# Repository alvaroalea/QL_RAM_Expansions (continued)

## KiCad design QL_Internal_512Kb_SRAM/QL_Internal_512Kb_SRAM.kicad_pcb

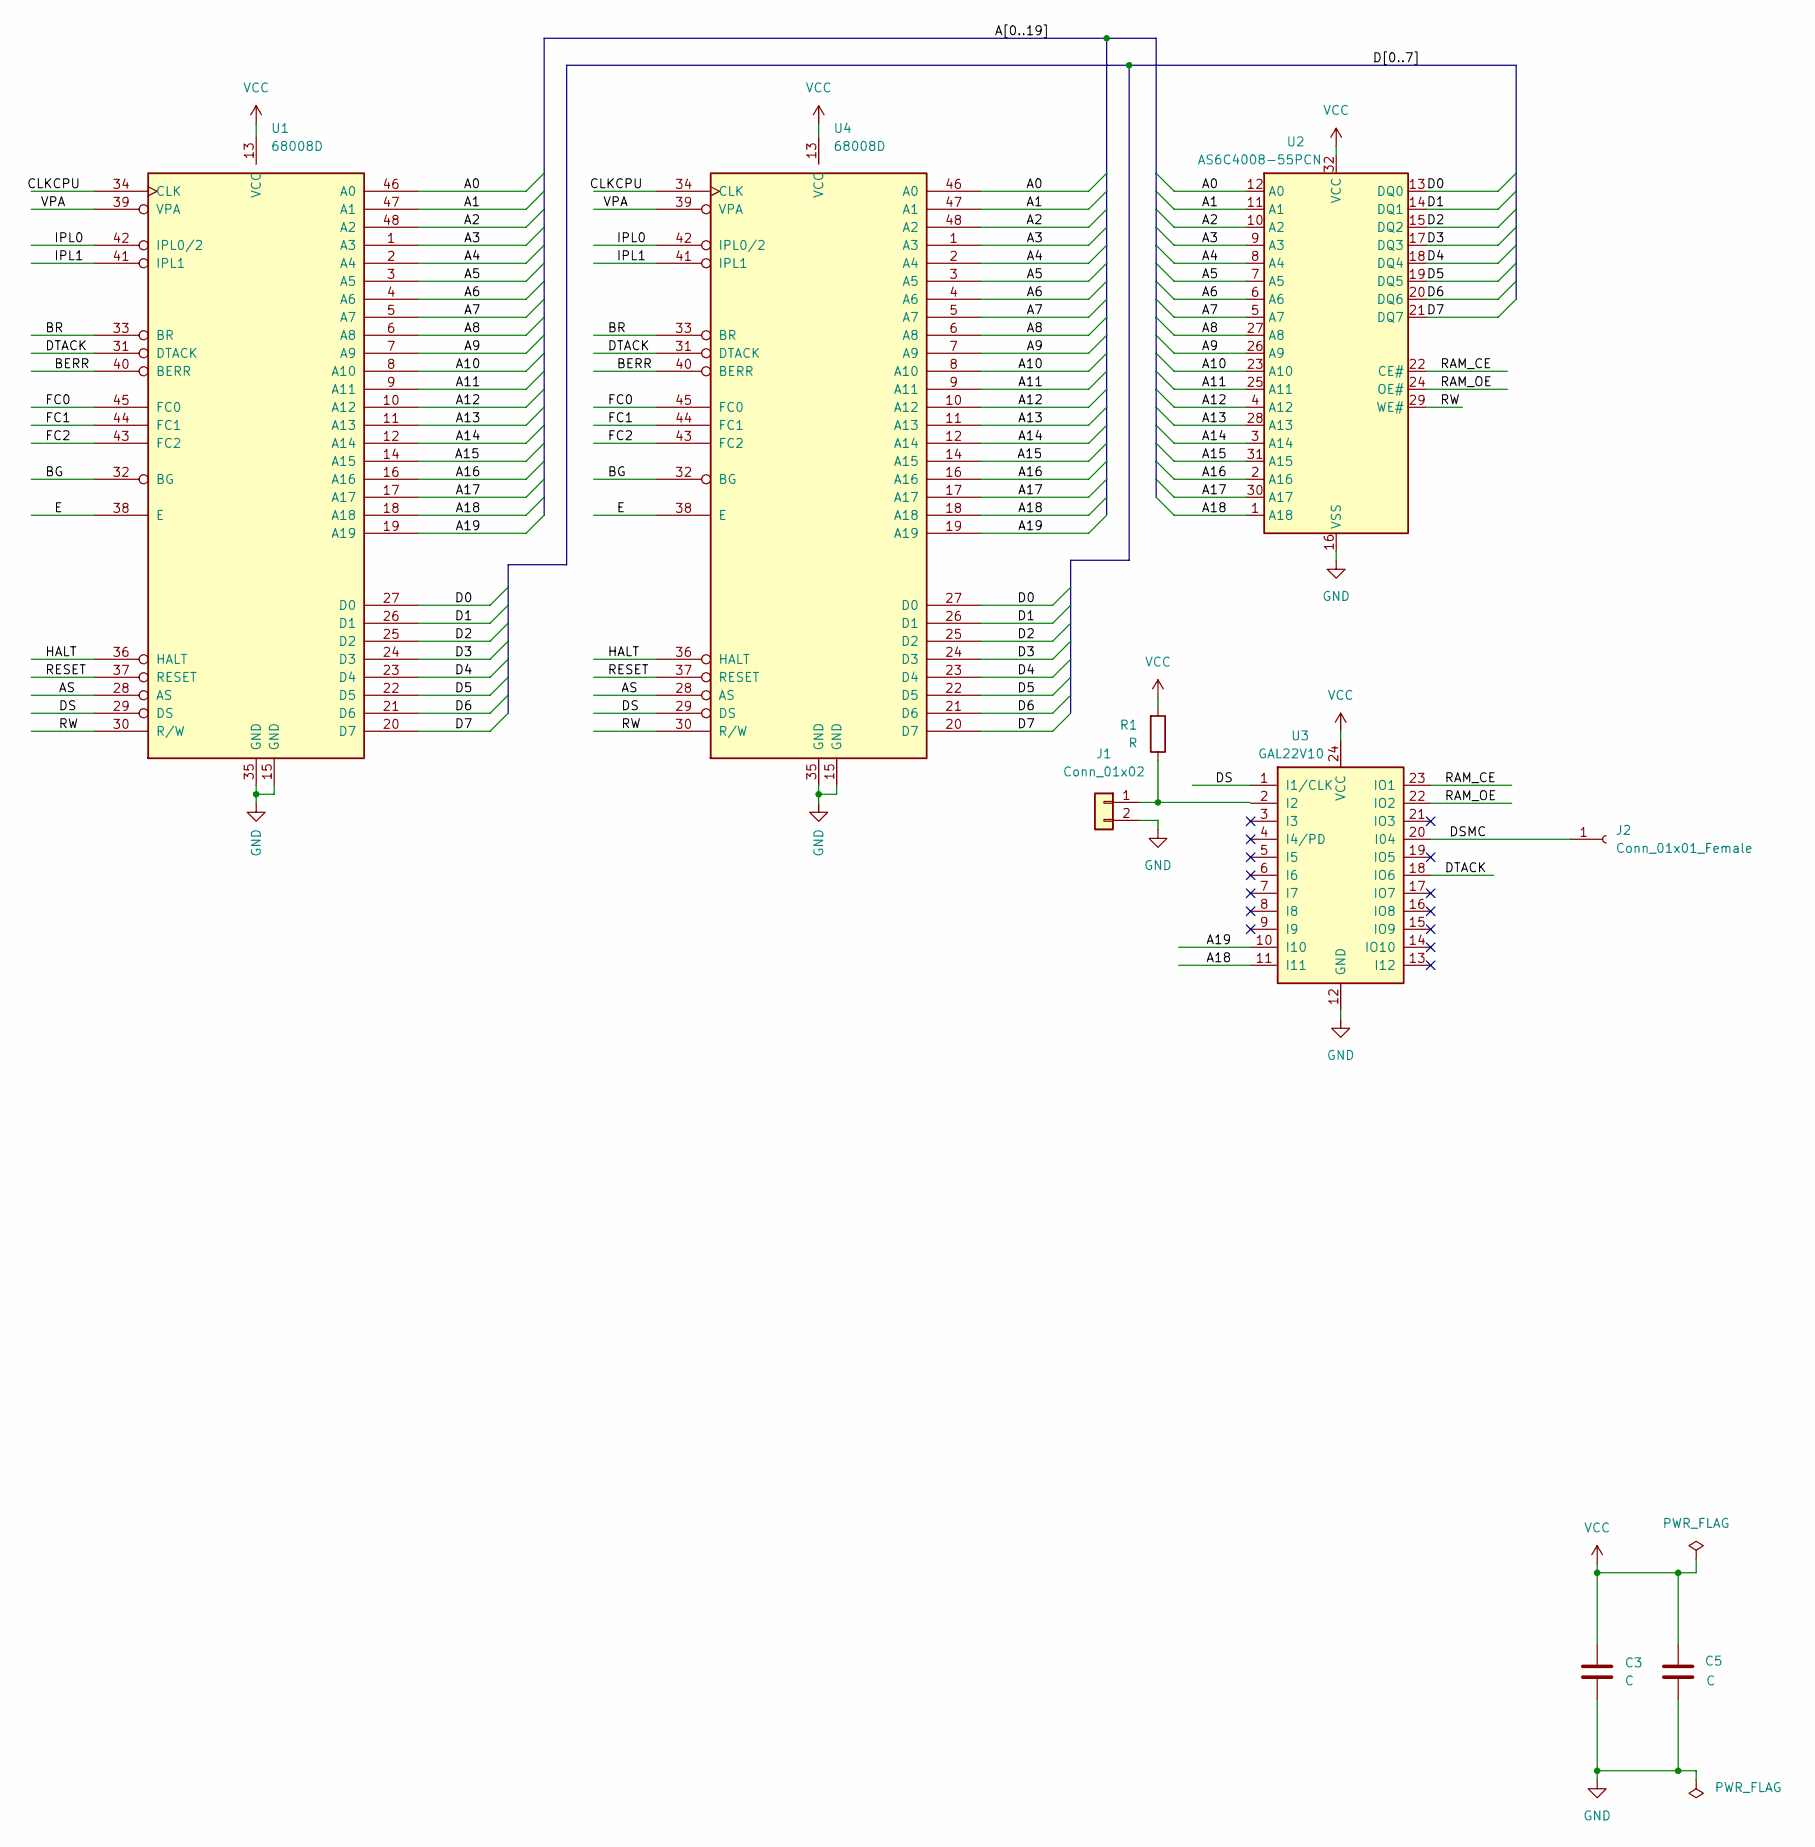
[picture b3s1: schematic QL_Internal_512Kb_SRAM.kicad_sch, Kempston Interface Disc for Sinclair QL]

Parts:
C3, C5: C; C_1206_3216Metric_Pad1.33x1.80mm_HandSolder
J1: Conn_01x02; PinHeader_1x02_P2.54mm_Vertical
J2: Conn_01x01_Female; PinHeader_1x01_P2.54mm_Vertical
R1: R; R_1206_3216Metric_Pad1.30x1.75mm_HandSolder
U1, U4: 68008D; DIP-48_W15.24mm_LongPads
U2: AS6C4008-55PCN; SSOP-32_11.305x20.495mm_P1.27mm
U3: GAL22V10; PLCC-28

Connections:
/A0: U1.46 (A0), U2.12 (A0), U4.46 (A0)
/A1: U1.47 (A1), U2.11 (A1), U4.47 (A1)
/A2: U1.48 (A2), U2.10 (A2), U4.48 (A2)
/A3: U1.1 (A3), U2.9 (A3), U4.1 (A3)
/A4: U1.2 (A4), U2.8 (A4), U4.2 (A4)
/A5: U1.3 (A5), U2.7 (A5), U4.3 (A5)
/A6: U1.4 (A6), U2.6 (A6), U4.4 (A6)
/A7: U1.5 (A7), U2.5 (A7), U4.5 (A7)
/A8: U1.6 (A8), U2.27 (A8), U4.6 (A8)
/A9: U1.7 (A9), U2.26 (A9), U4.7 (A9)
/A10: U1.8 (A10), U2.23 (A10), U4.8 (A10)
/A11: U1.9 (A11), U2.25 (A11), U4.9 (A11)
/A12: U1.10 (A12), U2.4 (A12), U4.10 (A12)
/A13: U1.11 (A13), U2.28 (A13), U4.11 (A13)
/A14: U1.12 (A14), U2.3 (A14), U4.12 (A14)
/A15: U1.14 (A15), U2.31 (A15), U4.14 (A15)
/A16: U1.16 (A16), U2.2 (A16), U4.16 (A16)
/A17: U1.17 (A17), U2.30 (A17), U4.17 (A17)
/A18: U1.18 (A18), U2.1 (A18), U3.11 (I11), U4.18 (A18)
/A19: U1.19 (A19), U3.10 (I10), U4.19 (A19)
/AS: U1.28 (AS), U4.28 (AS)
/BERR: U1.40 (BERR), U4.40 (BERR)
/BG: U1.32 (BG), U4.32 (BG)
/BR: U1.33 (BR), U4.33 (BR)
/CLKCPU: U1.34 (CLK), U4.34 (CLK)
/D0: U1.27 (D0), U2.13 (DQ0), U4.27 (D0)
/D1: U1.26 (D1), U2.14 (DQ1), U4.26 (D1)
/D2: U1.25 (D2), U2.15 (DQ2), U4.25 (D2)
/D3: U1.24 (D3), U2.17 (DQ3), U4.24 (D3)
/D4: U1.23 (D4), U2.18 (DQ4), U4.23 (D4)
/D5: U1.22 (D5), U2.19 (DQ5), U4.22 (D5)
/D6: U1.21 (D6), U2.20 (DQ6), U4.21 (D6)
/D7: U1.20 (D7), U2.21 (DQ7), U4.20 (D7)
/DS: U1.29 (DS), U3.1 (I1/CLK), U4.29 (DS)
/DSMC: J2.1, U3.20 (I04)
/DTACK: U1.31 (DTACK), U3.18 (IO6), U4.31 (DTACK)
/E: U1.38 (E), U4.38 (E)
/FC0: U1.45 (FC0), U4.45 (FC0)
/FC1: U1.44 (FC1), U4.44 (FC1)
/FC2: U1.43 (FC2), U4.43 (FC2)
/HALT: U1.36 (HALT), U4.36 (HALT)
/IPL0: U1.42 (IPL0/2), U4.42 (IPL0/2)
/IPL1: U1.41 (IPL1), U4.41 (IPL1)
/RAM_CE: U2.22 (CE#), U3.23 (IO1)
/RAM_OE: U2.24 (OE#), U3.22 (IO2)
/RESET: U1.37 (RESET), U4.37 (RESET)
/RW: U1.30 (R/W), U2.29 (WE#), U4.30 (R/W)
/VPA: U1.39 (VPA), U4.39 (VPA)
GND: C3.2, C5.1, J1.2, U1.15 (GND), U1.35 (GND), U2.16 (VSS), U3.12 (GND), U4.15 (GND), U4.35 (GND)
unnamed: J1.1, R1.1
VCC: C3.1, C5.2, R1.2, U1.13 (VCC), U2.32 (VCC), U3.24 (VCC), U4.13 (VCC)

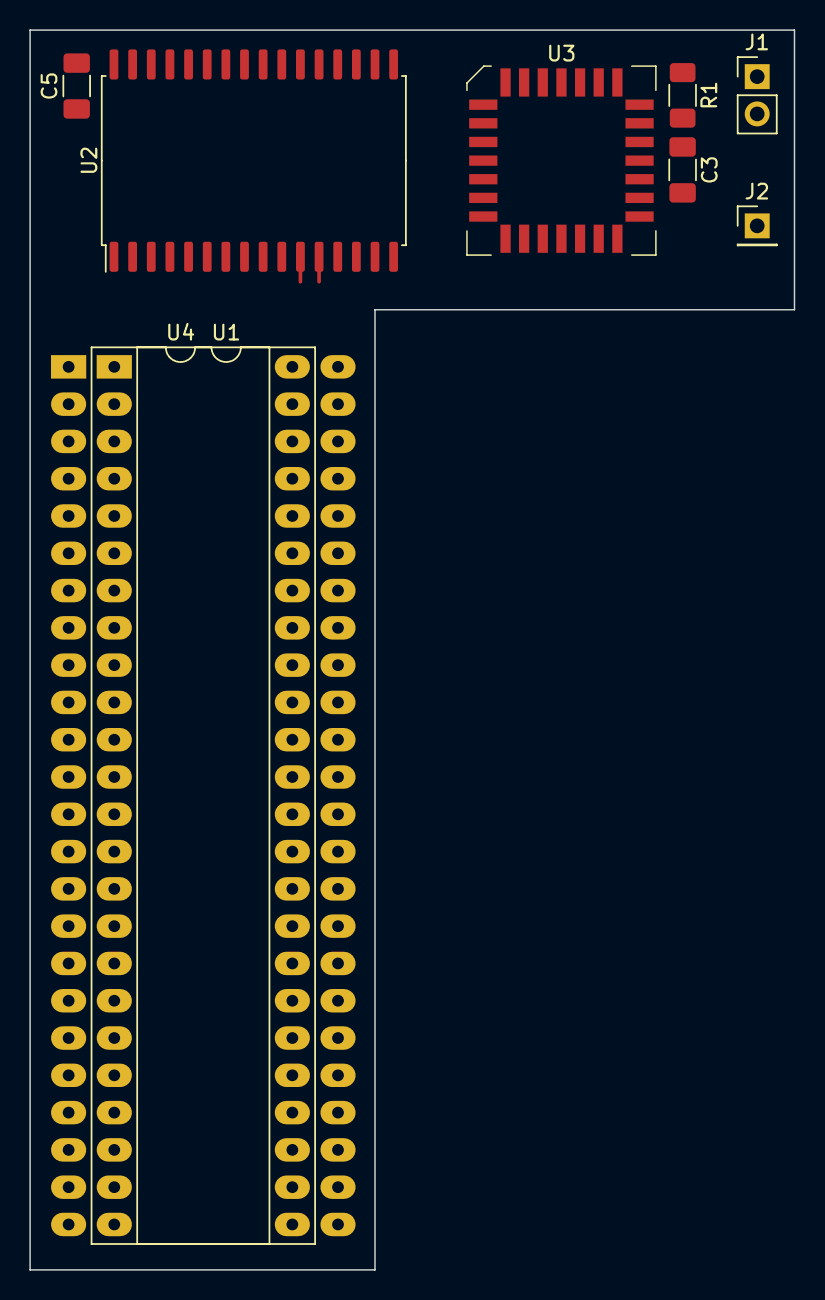
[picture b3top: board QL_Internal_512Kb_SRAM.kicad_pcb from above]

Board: 2 copper layers, 52.1 x 84.5 mm, 9 parts (0 on the bottom side), 51 nets.

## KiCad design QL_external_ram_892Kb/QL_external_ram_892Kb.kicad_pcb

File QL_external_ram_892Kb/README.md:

# SINCLAIR QL 896kB External Rom Expansion

(C) 2022 Alvaro Alea Fernandez

License under: CERN Open Hardware Licence Version 2 - Strongly Reciprocal

https://ohwr.org/cern_ohl_s_v2.txt

This is based on the work of McLeod Ideafix, Jose Leandro, Zerover and tcat between others. 

This board will provide up to 768kB aditional of static RAM (fast-ram) to the sinclair QL.

This board can be stacked with my old external ram board, jumpers allow a 512Kb, or +256Kb configs of the old board.

There is also a expecial 832Kb config that free the 64Kb top memory for aditional boards without use the ROM Cartridge area (Jose Leandro's QuBide...)

Provide a expansion conector to allow conect aditional interfaces.

There area available 4 configuration trough a dip switch in the PCB.
* 640kB - This is the standar 512kB expansion for any QL
* 832kB - Similar to 256kB provide aditional space for expansion cards correctly configured.
* 896kB - Maximin RAM do not provide aditional space for expansion cards.
* Expecial - This is for use as a second expansion, use the full QL space for a maximun of 898kB, be aware that this is incompatible with a lot of expansion card, so use with caution (Any expansion card that do not use jumper for configuration will be incompatible).

In the GAL folder there is the source code to be compiled with GALasm that you can found here: https://github.com/daveho/GALasm

## Mini Trump Card Compatibility

I have done a version of the trump card disk interface here: https://github.com/alvaroalea/QL_MiniTrump3 , this interface do not
provide memory like the original one. You can combine both cards to mimic the original trump card.

You shall connect this board after the minitrump, you need to change the solder jumper (JP1) to 1-2 to allow the Minitrump card to coordinate with the second memory card.

This jumper can be alwais 1-2, 2-3 is only used if you have another card that need BERR signal (none as far as I know).

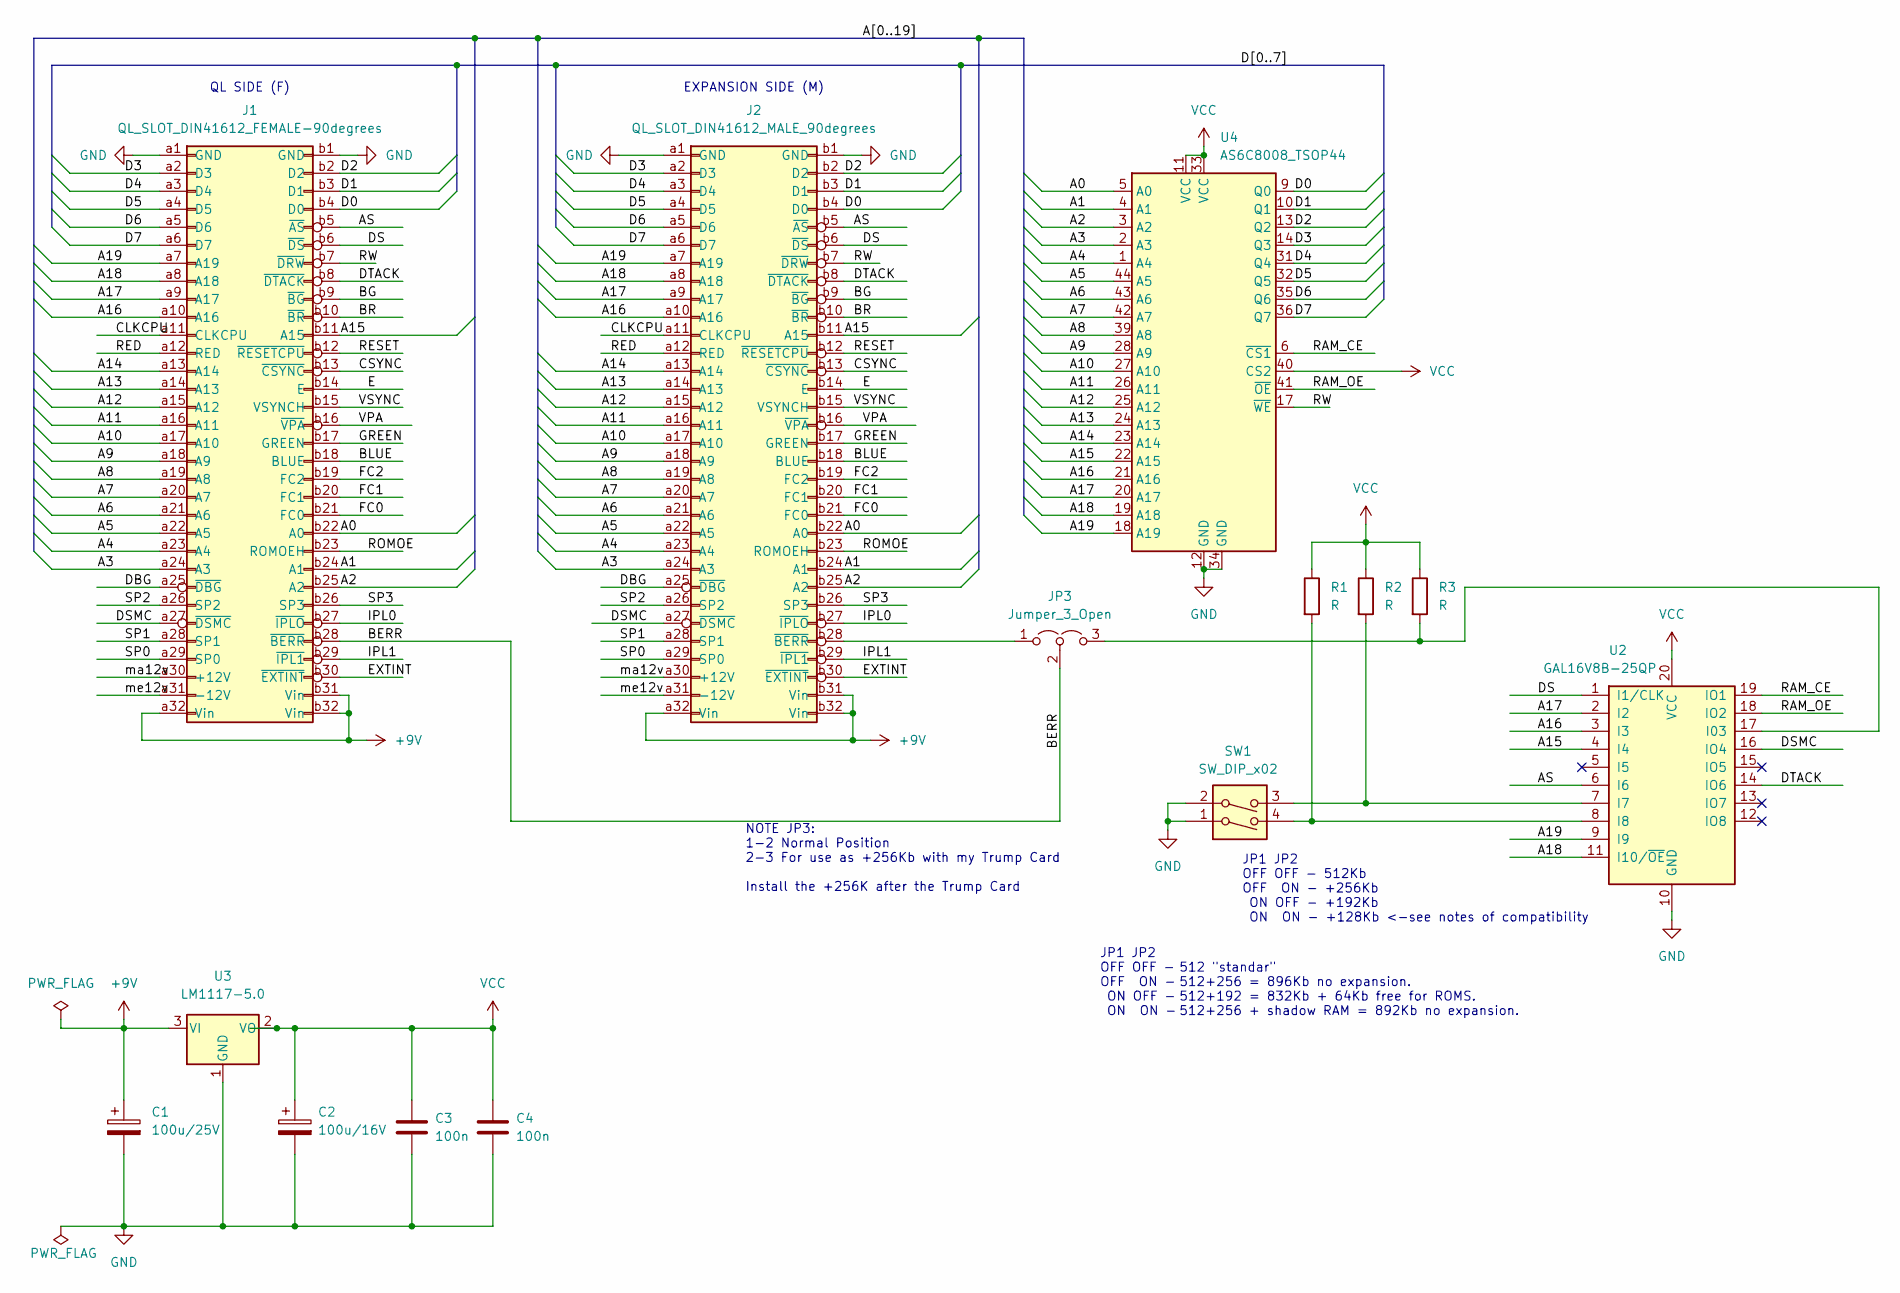
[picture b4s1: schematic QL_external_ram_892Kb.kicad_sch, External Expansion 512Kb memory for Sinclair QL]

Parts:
C1: 100u/25V; CP_Radial_D6.3mm_P2.50mm
C2: 100u/16V; CP_Radial_D6.3mm_P2.50mm
C3, C4: 100n; C_1206_3216Metric_Pad1.33x1.80mm_HandSolder
J1: QL_SLOT_DIN41612_FEMALE-90degrees; DIN41612_B_2x32_Female_Horizontal_THT
J2: QL_SLOT_DIN41612_MALE_90degrees; DIN41612_B_2x32_Male_Horizontal_THT
JP3: Jumper_3_Open; SolderJumper-3_P1.3mm_Open_Pad1.0x1.5mm
R1, R2, R3: R; R_1206_3216Metric_Pad1.30x1.75mm_HandSolder
SW1: SW_DIP_x02; DIP-4_W7.62mm_Socket
U2: GAL16V8B-25QP; DIP-20_W7.62mm_Socket
U3: LM1117-5.0; SOT-223-3_TabPin2
U4: AS6C8008_TSOP44; TSOP-II-44_10.16x18.41mm_P0.8mm

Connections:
+9V: C1.1, J1.a32 (Vin), J1.b31 (Vin), J1.b32 (Vin), J2.a32 (Vin), J2.b31 (Vin), J2.b32 (Vin), U3.3 (VI)
/A0: J1.b22 (A0), J2.b22 (A0), U4.5 (A0)
/A1: J1.b24 (A1), J2.b24 (A1), U4.4 (A1)
/A2: J1.b25 (A2), J2.b25 (A2), U4.3 (A2)
/A3: J1.a24 (A3), J2.a24 (A3), U4.2 (A3)
/A4: J1.a23 (A4), J2.a23 (A4), U4.1 (A4)
/A5: J1.a22 (A5), J2.a22 (A5), U4.44 (A5)
/A6: J1.a21 (A6), J2.a21 (A6), U4.43 (A6)
/A7: J1.a20 (A7), J2.a20 (A7), U4.42 (A7)
/A8: J1.a19 (A8), J2.a19 (A8), U4.39 (A8)
/A9: J1.a18 (A9), J2.a18 (A9), U4.28 (A9)
/A10: J1.a17 (A10), J2.a17 (A10), U4.27 (A10)
/A11: J1.a16 (A11), J2.a16 (A11), U4.26 (A11)
/A12: J1.a15 (A12), J2.a15 (A12), U4.25 (A12)
/A13: J1.a14 (A13), J2.a14 (A13), U4.24 (A13)
/A14: J1.a13 (A14), J2.a13 (A14), U4.23 (A14)
/A15: J1.b11 (A15), J2.b11 (A15), U2.4 (I4), U4.22 (A15)
/A16: J1.a10 (A16), J2.a10 (A16), U2.3 (I3), U4.21 (A16)
/A17: J1.a9 (A17), J2.a9 (A17), U2.2 (I2), U4.20 (A17)
/A18: J1.a8 (A18), J2.a8 (A18), U2.11 (I10/~OE), U4.19 (A18)
/A19: J1.a7 (A19), J2.a7 (A19), U2.9 (I9), U4.18 (A19)
/AS: J1.b5 (~AS), J2.b5 (~AS), U2.6 (I6)
/BERR: J1.b28 (~BERR), JP3.2 (C)
/BG: J1.b9 (~BG), J2.b9 (~BG)
/BLUE: J1.b18 (BLUE), J2.b18 (BLUE)
/BR: J1.b10 (~BR), J2.b10 (~BR)
/CLKCPU: J1.a11 (CLKCPU), J2.a11 (CLKCPU)
/CSYNC: J1.b13 (~CSYNC), J2.b13 (~CSYNC)
/D0: J1.b4 (D0), J2.b4 (D0), U4.9 (Q0)
/D1: J1.b3 (D1), J2.b3 (D1), U4.10 (Q1)
/D2: J1.b2 (D2), J2.b2 (D2), U4.13 (Q2)
/D3: J1.a2 (D3), J2.a2 (D3), U4.14 (Q3)
/D4: J1.a3 (D4), J2.a3 (D4), U4.31 (Q4)
/D5: J1.a4 (D5), J2.a4 (D5), U4.32 (Q5)
/D6: J1.a5 (D6), J2.a5 (D6), U4.35 (Q6)
/D7: J1.a6 (D7), J2.a6 (D7), U4.36 (Q7)
/DBG: J1.a25 (~DBG), J2.a25 (~DBG)
/DS: J1.b6 (~DS), J2.b6 (~DS), U2.1 (I1/CLK)
/DSMC: J1.a27 (~DSMC), J2.a27 (~DSMC), U2.16 (IO4)
/DTACK: J1.b8 (~DTACK), J2.b8 (~DTACK), U2.14 (IO6)
/E: J1.b14 (E), J2.b14 (E)
/EXTINT: J1.b30 (~EXTINT), J2.b30 (~EXTINT)
/FC0: J1.b21 (FC0), J2.b21 (FC0)
/FC1: J1.b20 (FC1), J2.b20 (FC1)
/FC2: J1.b19 (FC2), J2.b19 (FC2)
/GREEN: J1.b17 (GREEN), J2.b17 (GREEN)
/IPL0: J1.b27 (~IPLO), J2.b27 (~IPLO)
/IPL1: J1.b29 (~IPL1), J2.b29 (~IPL1)
/RAM_CE: U2.19 (IO1), U4.6 (~CS1)
/RAM_OE: U2.18 (IO2), U4.41 (~OE)
/RED: J1.a12 (RED), J2.a12 (RED)
/RESET: J1.b12 (~RESETCPU), J2.b12 (~RESETCPU)
/ROMOE: J1.b23 (ROMOEH), J2.b23 (ROMOEH)
/RW: J1.b7 (~DRW), J2.b7 (~DRW), U4.17 (~WE)
/SP0: J1.a29 (SP0), J2.a29 (SP0)
/SP1: J1.a28 (SP1), J2.a28 (SP1)
/SP2: J1.a26 (SP2), J2.a26 (SP2)
/SP3: J1.b26 (SP3), J2.b26 (SP3)
/VPA: J1.b16 (~VPA), J2.b16 (~VPA)
/VSYNC: J1.b15 (VSYNCH), J2.b15 (VSYNCH)
/ma12v: J1.a30 (+12V), J2.a30 (+12V)
/me12v: J1.a31 (-12V), J2.a31 (-12V)
GND: C1.2, C2.2, C3.2, C4.2, J1.a1 (GND), J1.b1 (GND), J2.a1 (GND), J2.b1 (GND), SW1.1, SW1.2, U2.10 (GND), U3.1 (GND), U4.12 (GND), U4.34 (GND)
unnamed: J2.b28 (~BERR), JP3.1 (A)
unnamed: JP3.3 (B), R3.2, U2.17 (I03)
unnamed: R2.2, SW1.3, U2.7 (I7)
unnamed: R1.2, SW1.4, U2.8 (I8)
VCC: C2.1, C3.1, C4.1, R1.1, R2.1, R3.1, U2.20 (VCC), U3.2 (VO), U4.11 (VCC), U4.33 (VCC), U4.40 (CS2)

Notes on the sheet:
NOTE JP3: 1-2 Normal Position 2-3 For use as +256Kb with my Trump Card Install the +256K after the Trump Card
512 "standar" 512+256 = 896Kb no expansion. 512+192 = 832Kb + 64Kb free for ROMS. 512+256 + shadow RAM = 892Kb no expansion.
EXPANSION SIDE (M)
JP1 JP2 OFF OFF - 512Kb OFF ON - +256Kb ON OFF - +192Kb ON ON - +128Kb <-see notes of compatibility
QL SIDE (F)
JP1 JP2 OFF OFF - OFF ON - ON OFF - ON ON -

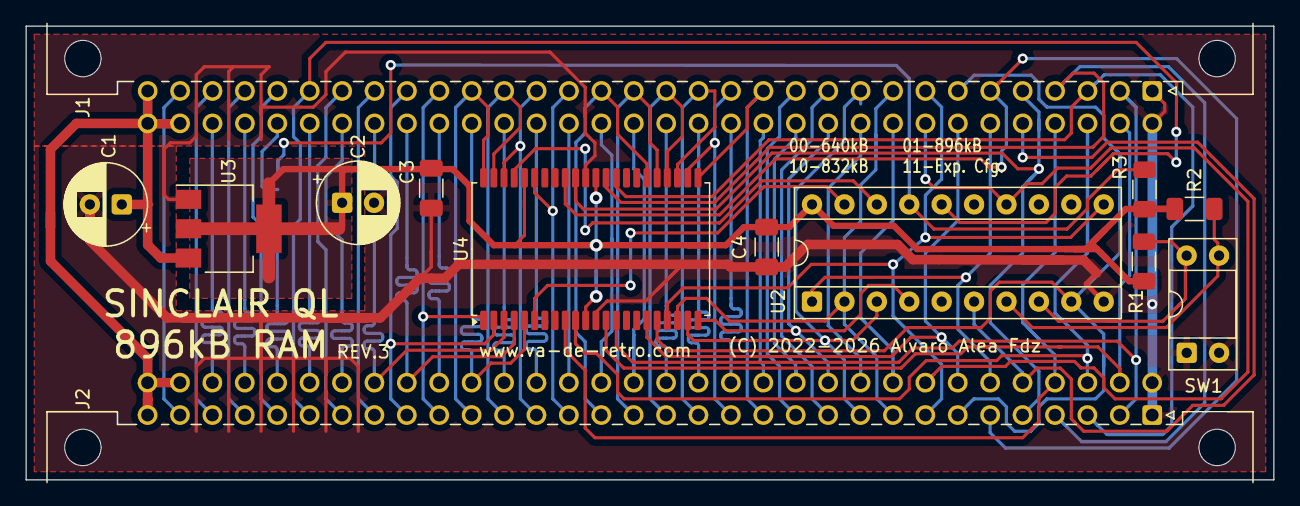
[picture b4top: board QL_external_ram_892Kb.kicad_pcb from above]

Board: 2 copper layers, 97.8 x 35.6 mm, 14 parts (1 on the bottom side), 68 nets.

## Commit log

2026-03-20 new boards, and reorganization
2026-03-20 cosmetic changes
2026-03-20 readme
2026-03-20 896 :-D
2026-03-20 WIP internal
2026-03-20 add ramrom
2026-03-21 initial miracle
2026-03-22 miracle card works
2026-03-22 work on miracle
2026-03-23 Miracle RAM probably finished
